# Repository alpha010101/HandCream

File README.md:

###
RP2040を使ったマイコン基板で、基本的にはRaspberry-pi pico互換。

24V系の機器を制御するのが目的で、そのために東芝のDMOS-SINKドライバTBD62064が載っている。本当ならカプラで分離するのが適当なのだろうが、こんなもんで問題なく動いてる

電源は24VをXHコネクタから入れる想定。それをTIのUA78M05で5V/0.5Aに落とし、それを更にMicrochipのMIC5504で3.3V/0.3Aに落としている。3.3VはMCU用、5VはLEDと冷却ファンの駆動用

SchematicsとPCB-LayoutはAutodesk-Eagle無償版を使用し、elecrowで製造することを想定したガーバーを作成している

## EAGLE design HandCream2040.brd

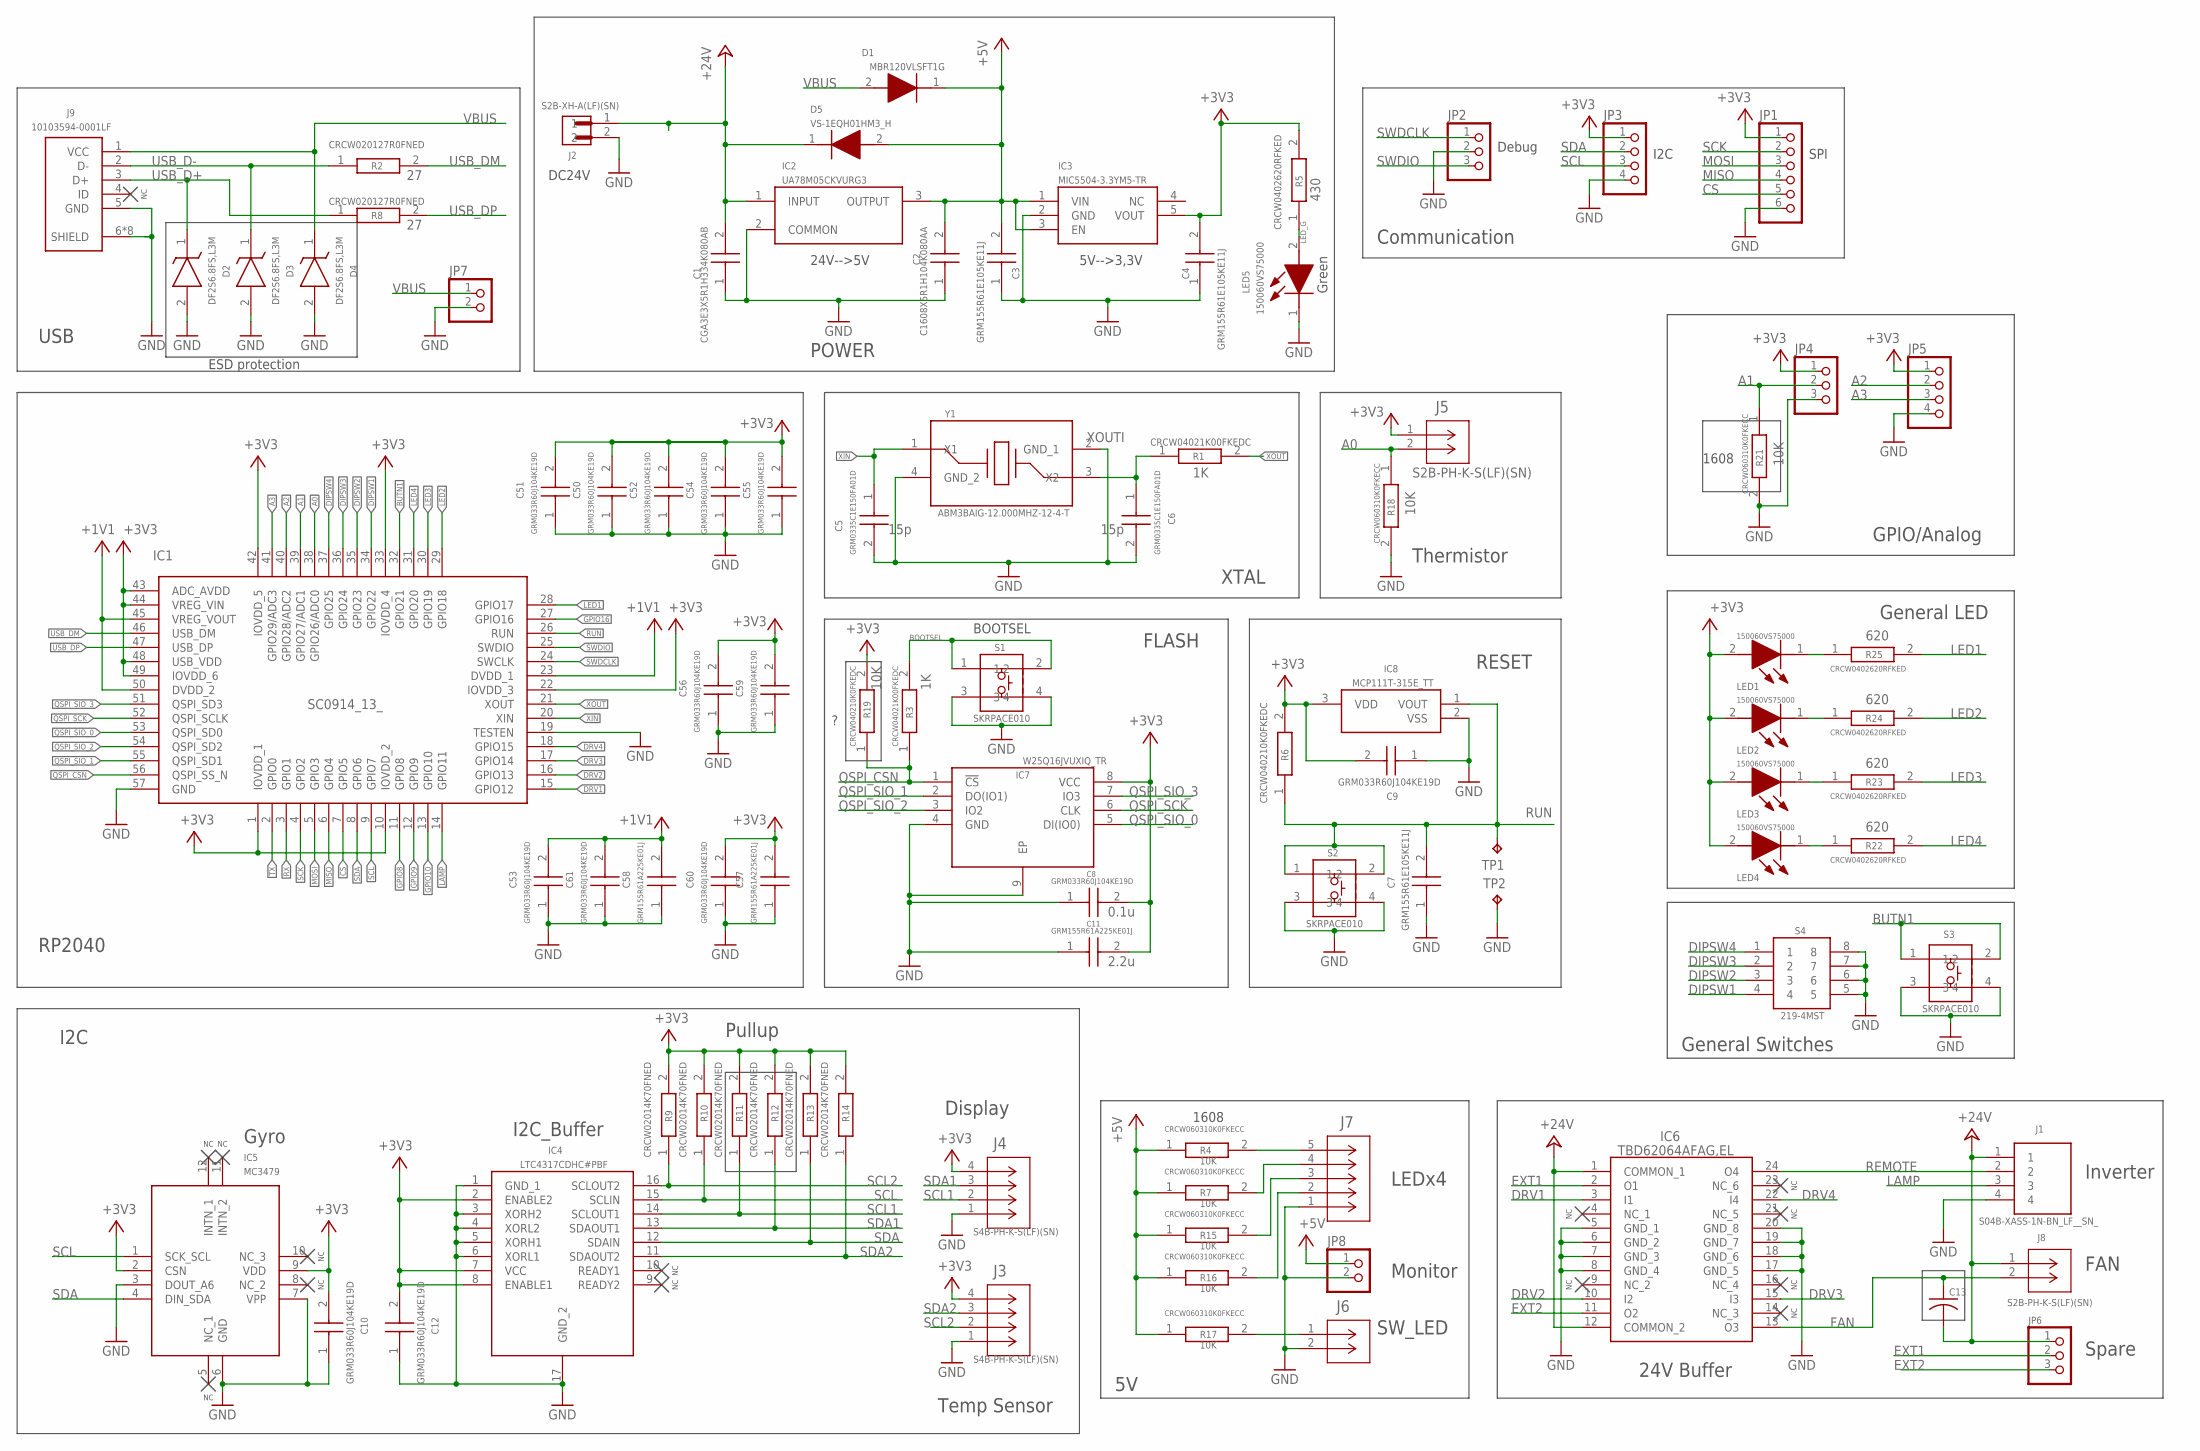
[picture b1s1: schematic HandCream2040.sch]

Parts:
C1: CGA3E3X5R1H334K080AB; CAPC1608X90N
C2: C1608X5R1H104K080AA; CAPC1608X80N
C3, C4, C7: GRM155R61E105KE11J; CAPC1005X55N
C5, C6: GRM0335C1E150FA01D; CAPC0603X33N
C8, C9, C10, C12, C50, C51, C52, C53, C54, C55, C56, C59, C60, C61: GRM033R60J104KE19D; CAPC0603X33N
C11, C57, C58: GRM155R61A225KE01J; CAPC1005X55N
C13: C-US025-024X044; C025-024X044
D1: MBR120VLSFT1G; SODFL3616X98N
D2, D3, D4: DF2S6.8FS,L3M; SODFL1006X45N
D5: VS-1EQH01HM3_H; VS1EQH01HM3H
IC1: SC0914_13_; SC091413
IC2: UA78M05CKVURG3; TPS7A6533QKVURQ1
IC3: MIC5504-3.3YM5-TR; SOT95P280X145-5N
IC4: LTC4317CDHC#PBF; SON50P300X500X80-17N
IC5: MC3479
IC6: TBD62064AFAG,EL; SOP100P800X190-24N
IC7: W25Q16JVUXIQ_TR; SON50P300X200X60-9N
IC8: MCP111T-315E_TT; SOT96P237X112-3N
J1: S04B-XASS-1N-BN_LF__SN_; S04BXASS1NBNLFSN
J2: S2B-XH-A(LF)(SN); JST_S2B-XH-A(LF)(SN)
J3, J4: S4B-PH-K-S(LF)(SN); CONN_S4B-PH-K-S_JST
J5, J6, J8: S2B-PH-K-S(LF)(SN); CONN_S2B-PH-K-S_JST
J7: S5B-PH-K-S_(LF)(SN); CONN_S5B-PH-K-S_JST
J9: 10103594-0001LF; AMPHENOL_10103594-0001LF
JP1: PINHD-1X6; 1X06
JP2, JP4, JP6: PINHD-1X3; 1X03
JP3, JP5: PINHD-1X4; 1X04
JP7, JP8: PINHD-1X2; 1X02
LED1, LED2, LED3, LED4, LED5: 150060VS75000; LEDC1608X80N
R1, R3: CRCW04021K00FKEDC; RESC1005X35N
R2, R8: CRCW020127R0FNED; RESC0603X28N
R4, R7, R15, R16, R17, R18, R21: CRCW060310K0FKECC; RESC1608X55N
R5, R22, R23, R24, R25: CRCW0402620RFKED; RESC1005X40N
R6, R19: CRCW040210K0FKEDC; RESC1005X35N
R9, R10, R11, R12, R13, R14: CRCW02014K70FNED; RESC0603X28N
S1, S2, S3: SKRPACE010; SMT(4.2X3.2)
S4: 219-4MST; 2194MST
TP1, TP2: TPB1,27; B1,27
Y1: ABM3BAIG-12.000MHZ-12-4-T; ABM3BAIG

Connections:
+1V1: C53.2, C58.2, C61.2, IC1.23 (DVDD_1), IC1.45 (VREG_VOUT), IC1.50 (DVDD_2)
+3V3: C4.2, C8.2, C9.2, C10.2, C11.2, C12.2, C50.2, C51.2, C52.2, C54.2, C55.2, C56.2, C57.2, C59.2, C60.2, IC1.1 (IOVDD_1), IC1.10 (IOVDD_2), IC1.22 (IOVDD_3), IC1.33 (IOVDD_4), IC1.42 (IOVDD_5), IC1.43 (ADC_AVDD), IC1.44 (VREG_VIN), IC1.48 (USB_VDD), IC1.49 (IOVDD_6), IC3.5 (VOUT), IC4.2 (ENABLE2), IC4.7 (VCC), IC4.8 (ENABLE1), IC5.2 (CSN), IC5.9 (VDD), IC7.8 (VCC), IC8.3 (VDD), J3.4, J4.4, J5.1, JP1.1, JP3.1, JP4.1, JP5.1, LED1.2 (A), LED2.2 (A), LED3.2 (A), LED4.2 (A), R5.2, R6.2, R9.2, R10.2, R11.2, R12.2, R13.2, R14.2, R19.2
+5V: C2.2, C3.2, D1.1 (K), D5.2 (A), IC2.3 (OUTPUT), IC3.1 (VIN), IC3.3 (EN), JP8.1, R4.1, R7.1, R15.1, R16.1, R17.1
+24V: C1.2, C13.2, D5.1 (K), IC2.1 (INPUT), IC6.1 (COMMON_1), IC6.12 (COMMON_2), J1.1, J2.1, J8.1, JP6.1
A0: IC1.38 (GPIO26/ADC0), J5.2, R18.1
A1: IC1.39 (GPIO27/ADC1), JP4.2, R21.1
A2: IC1.40 (GPIO28/ADC2), JP5.2
A3: IC1.41 (GPIO29/ADC3), JP5.3
BOOTSEL: R3.2, S1.1, S1.2
BUTN1: IC1.32 (GPIO21), S3.1, S3.2
CS: IC1.7 (GPIO5), JP1.5
DIPSW1: IC1.34 (GPIO22), S4.4
DIPSW2: IC1.35 (GPIO23), S4.3
DIPSW3: IC1.36 (GPIO24), S4.2
DIPSW4: IC1.37 (GPIO25), S4.1
DRV1: IC1.15 (GPIO12), IC6.3 (I1)
DRV2: IC1.16 (GPIO13), IC6.10 (I2)
DRV3: IC1.17 (GPIO14), IC6.15 (I3)
DRV4: IC1.18 (GPIO15), IC6.22 (I4)
EXT1: IC6.2 (O1), JP6.2
EXT2: IC6.11 (O2), JP6.3
FAN: C13.1, IC6.13 (O3), J8.2
GND: C1.1, C2.1, C3.1, C4.1, C5.2, C6.2, C7.1, C8.1, C9.1, C10.1, C11.1, C12.1, C50.1, C51.1, C52.1, C53.1, C54.1, C55.1, C56.1, C57.1, C58.1, C59.1, C60.1, C61.1, D2.2 (A), D3.2 (A), D4.2 (A), IC1.19 (TESTEN), IC1.57 (GND), IC2.2 (COMMON), IC3.2 (GND), IC4.1 (GND_1), IC4.3 (XORH2), IC4.4 (XORL2), IC4.5 (XORH1), IC4.6 (XORL1), IC4.17 (GND_2), IC5.3 (DOUT_A6), IC5.6 (GND), IC5.7 (VPP), IC6.5 (GND_1), IC6.6 (GND_2), IC6.7 (GND_3), IC6.8 (GND_4), IC6.17 (GND_5), IC6.18 (GND_6), IC6.19 (GND_7), IC6.20 (GND_8), IC7.4 (GND), IC7.9 (EP), IC8.2 (VSS), J1.4, J2.2, J3.1, J4.1, J6.2, J7.1, J9.5 (GND), J9.6 (SHIELD), J9.7 (SHIELD), J9.8 (SHIELD), J9.9 (SHIELD), J9.10 (SHIELD), J9.11 (SHIELD), J9.S1 (SHIELD), J9.S2 (SHIELD), JP1.6, JP2.2, JP3.4, JP4.3, JP5.4, JP7.2, JP8.2, LED5.1 (K), R18.2, R21.2, S1.3, S1.4, S2.3, S2.4, S3.3, S3.4, S4.5, S4.6, S4.7, S4.8, TP2.TP, Y1.2 (GND_1), Y1.4 (GND_2)
GPIO8: IC1.11 (GPIO8)
GPIO9: IC1.12 (GPIO9)
GPIO10: IC1.13 (GPIO10)
GPIO16: IC1.27 (GPIO16)
LAMP: IC1.14 (GPIO11), J1.3
LED1: IC1.28 (GPIO17), R25.2
LED2: IC1.29 (GPIO18), R24.2
LED3: IC1.30 (GPIO19), R23.2
LED4: IC1.31 (GPIO20), R22.2
LED_G: LED5.2 (A), R5.1
MISO: IC1.6 (GPIO4), JP1.4
MOSI: IC1.5 (GPIO3), JP1.3
unnamed: J7.5, R4.2
unnamed: J7.4, R7.2
unnamed: J7.3, R15.2
unnamed: J7.2, R16.2
unnamed: J6.1, R17.2
unnamed: LED1.1 (K), R25.1
unnamed: LED2.1 (K), R24.1
unnamed: LED3.1 (K), R23.1
unnamed: LED4.1 (K), R22.1
QSPI_CSN: IC1.56 (QSPI_SS_N), IC7.1 (!CS), R3.1, R19.1
QSPI_SCK: IC1.52 (QSPI_SCLK), IC7.6 (CLK)
QSPI_SIO_0: IC1.53 (QSPI_SD0), IC7.5 (DI(IO0))
QSPI_SIO_1: IC1.55 (QSPI_SD1), IC7.2 (DO(IO1))
QSPI_SIO_2: IC1.54 (QSPI_SD2), IC7.3 (IO2)
QSPI_SIO_3: IC1.51 (QSPI_SD3), IC7.7 (IO3)
REMOTE: IC6.24 (O4), J1.2
RUN: C7.2, IC1.26 (RUN), IC8.1 (VOUT), R6.1, S2.1, S2.2, TP1.TP
RX: IC1.3 (GPIO1)
SCK: IC1.4 (GPIO2), JP1.2
SCL: IC1.9 (GPIO7), IC4.15 (SCLIN), IC5.1 (SCK_SCL), JP3.3, R10.1
SCL1: IC4.14 (SCLOUT1), J4.2, R11.1
SCL2: IC4.16 (SCLOUT2), J3.2, R9.1
SDA: IC1.8 (GPIO6), IC4.12 (SDAIN), IC5.4 (DIN_SDA), JP3.2, R13.1
SDA1: IC4.13 (SDAOUT1), J4.3, R12.1
SDA2: IC4.11 (SDAOUT2), J3.3, R14.1
SWDCLK: IC1.24 (SWCLK), JP2.1
SWDIO: IC1.25 (SWDIO), JP2.3
TX: IC1.2 (GPIO0)
USB_D+: D2.1 (K), J9.3 (D+), R8.1
USB_D-: D3.1 (K), J9.2 (D-), R2.1
USB_DM: IC1.46 (USB_DM), R2.2
USB_DP: IC1.47 (USB_DP), R8.2
VBUS: D1.2 (A), D4.1 (K), J9.1 (VCC), JP7.1
XIN: C5.1, IC1.20 (XIN), Y1.1 (X1)
XOUT: IC1.21 (XOUT), R1.2
XOUTI: C6.1, R1.1, Y1.3 (X2)

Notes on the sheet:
USB
POWER
RP2040
FLASH
XTAL
RESET
BOOTSEL
I2C
Gyro
Display
Temp Sensor
LEDx4
SW_LED
24V Buffer
Monitor
Inverter
FAN
Spare
Thermistor
General Switches
Green
24V-->5V
5V-->3,3V
DC24V
Debug
I2C_Buffer
Pullup
General LED
SPI
Communication
GPIO/Analog
ESD protection
1608

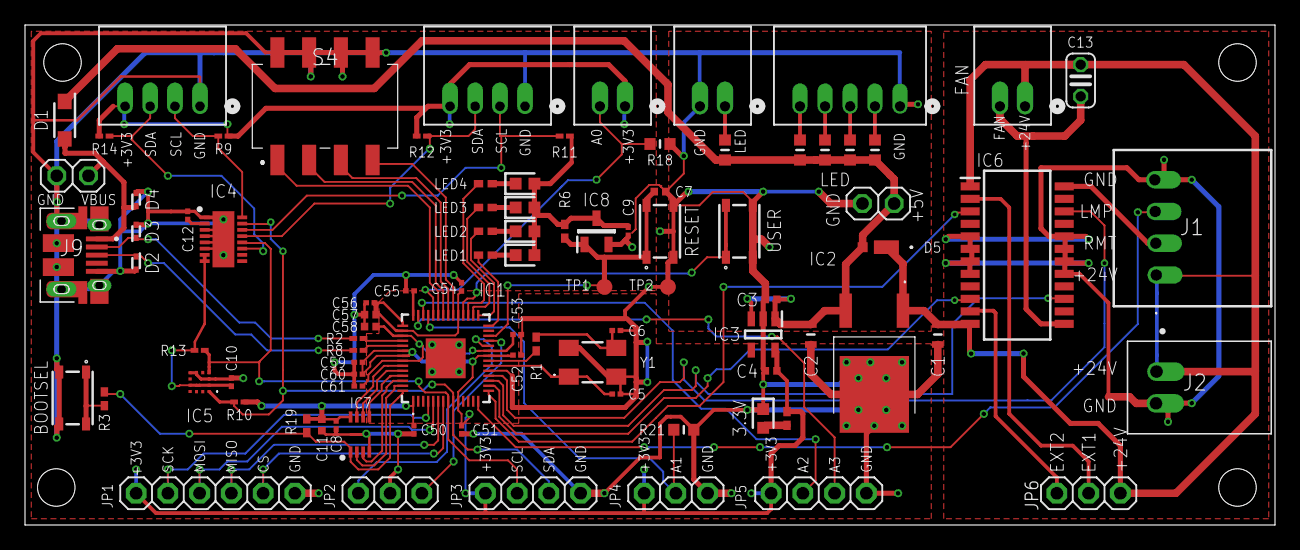
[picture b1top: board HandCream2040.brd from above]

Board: 2 copper layers, 100.0 x 40.0 mm, 91 parts (0 on the bottom side), 65 nets.

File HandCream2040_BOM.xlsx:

| Part# | Device | Qty | Manufacturer | Package | Value | Description | Source | MOUSER_PART_NUMBER | MOUSER_PRICE-STOCK
 | C1 | CGA3E3X5R1H334K080AB | 1 | TDK | CAPC1608X90N | 0.33uF | Multilayer Ceramic Capacitor, 50V, 10%, X5R, 1608 (0603), Or equivalent | mouser or Elecrow | 810-CGA3E3X5R1H334KB | https://www.mouser.co.uk/ProductDetail/TDK/CGA3E3X5R1H334K08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
 | C2 | C1608X5R1H104K080AA | 1 | TDK | CAPC1608X80N | 0.1uF | Multilayer Ceramic Capacitor, 50V, 10%, X5R, 1608 (0603), Or equivalent | mouser or Elecrow | 810-C1608X5R1H104K | https://www.mouser.co.uk/ProductDetail/TDK/C1608X5R1H104K080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
 | C3,C4,C7 | GRM155R61E105KE11J | 3 | Murata Electronics | CAPC1005X55N | 1uF | Multilayer Ceramic Capacitor, 25V, 10%, X5R, 1005 (0402), Or equivalent | mouser or Elecrow | 81-GRM155R61E105KE1J | https://www.mouser.co.uk/ProductDetail/Murata-Electronics/GR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
 | C5,C6 | GRM0335C1E150FA01D | 2 | Murata Electronics | CAPC0603X33N | 15pF | Multilayer Ceramic Capacitor, 25V, 1%, C0G, 0603 (0201), Or equivalent | mouser or Elecrow | 81-GRM0335C1E150FA1D | https://www.mouser.co.uk/ProductDetail/Murata-Electronics/GR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
 | C8,C9,C10,C12,C50,C51,C52, C53,C54,C55,C56,C59,C60,C61 | GRM033R60J104KE19D | 14 | Murata Electronics | CAPC0603X33N | 0.1uF | Multilayer Ceramic Capacitor, 6.3V, 10%, X5R, 0603 (0201), Or equivalent | mouser or Elecrow | 81-GRM033R60J104KE19 | https://www.mouser.co.uk/ProductDetail/Murata-Electronics/GR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
 | C11,C57,C58 | GRM155R61A225KE01J | 3 | Murata Electronics | CAPC1005X55N | 2.2uF | Multilayer Ceramic Capacitor, 10V, 10%, X5R, 1005 (0402), Or equivalent | mouser or Elecrow | 81-GRM155R61A225K01J | https://www.mouser.co.uk/ProductDetail/Murata-Electronics/GR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
 | C13 |  | 0 |  |  |  | No need to assemble
 | D1 | MBR120VLSFT1G | 1 | onsemi | SODFL3616X98N |  | Diode Schottky 20V, 1A, SOD-123FL | mouser or Elecrow | 863-MBR120VLSFT1G | https://www.mouser.co.uk/ProductDetail/onsemi/MBR120VLSFT1G?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
 | D2,D3,D4 | DF2S6.8FS,L3M | 0 | Toshiba | SODFL1006X45N |  | No need to assemble
 | D5 | VS-1EQH01HM3_H | 1 | Vishay | VS1EQH01HM3H |  | Rectifiers 100V 1A Fred Pt MicroSMP (DO-219AD) | mouser or Elecrow | 78-VS-1EQH01HM3/H | https://www.mouser.co.uk/ProductDetail/Vishay-Semiconductors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
 | IC1 | SC0914(13) / RP2040 | 1 | RASPBERRY-PI | SC091413 |  | ARM Cortex-M0+ - Microcontroller IC 32-Bit Dual-Core 133MHz External Program Me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 | mouser or Elecrow | 358-SC091413 | https://www.mouser.co.uk/ProductDetail/Raspberry-Pi/SC091413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
 | IC2 | UA78M05CKVURG3 | 1 | Texas Instruments | TPS7A6533QKVURQ1 |  | Linear Voltage Regulators, 500mA, 5V-output, max25V, | mouser or Elecrow | 595-UA78M05CKVURG3 | https://www.mouser.co.uk/ProductDetail/Texas-Instruments/UA7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
 | IC3 | MIC5504-3.3YM5-TR | 1 | Microchip | SOT95P280X145-5N |  | LDO Voltage Regulators, 300mA, 3.3V-output, max5.5V, SOT-23-5 | mouser or Elecrow | 998-MIC5504-3.3YM5TR | https://www.mouser.co.uk/ProductDetail/Microchip-Technology/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
 | IC4 | LTC4317CDHC#PBF | 1 | Analog Devices | SON50P300X500X80-17N |  | Specialized Interface, I2C, SMBus, I2C Bus & SMBus Systems Applications, Server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 | mouser or Elecrow | 584-LTC4317CDHC#PBF | https://www.mouser.com/Search/Refine.aspx?Keyword=584-LTC431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
 | IC5 | MC3479 | 1 | MEMSIC | MC3479 |  | Accelerometers Small Digital 3-axis Accelerometer Sensor | mouser or Elecrow | 498-MC3479 | https://www.mouser.co.uk/ProductDetail/MEMSIC/MC3479?qs=OlC7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
 | IC6 | TBD62064AFAG,EL | 1 | Toshiba | SOP100P800X190-24N |  | Gate Drivers DMOS Transistor Array 50V 1500mA | mouser or Elecrow | 757-TBD62064AFAGEHZ | https://www.mouser.co.uk/ProductDetail/Toshiba/TBD62064AFAGE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
 | IC7 | W25Q16JVUXIQ_TR | 1 | Winbond | SON50P300X200X60-9N |  | NOR Flash spiFlash, 3V, 16M-bit, 4Kb Uniform Sector, DTR | mouser or Elecrow | 454-W25Q16JVUXIQTR | https://www.mouser.co.uk/ProductDetail/Winbond/W25Q16JVUXIQ-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
 | IC8 | MCP111T-315E_TT | 1 | Microchip | SOT96P237X112-3N |  | Voltage Supervisor 3.003 3.157 V, 3-Pin SOT-23B | mouser or Elecrow | 579-MCP111T-315E/TT | https://www.mouser.co.uk/ProductDetail/Microchip-Technology/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
 | J1 | S04B-XASS-1N-BN_LF__SN_ | 0 | JST | S04BXASS1NBNLFSN |  | No need to assemble
 | J2 | S2B-XH-A(LF)(SN) | 0 | JST | JST_S2B-XH-A(LF)(SN) |  | No need to assemble
 | J3,J4 | S4B-PH-K-S(LF)(SN) | 0 | JST | CONN_S4B-PH-K-S_JST |  | No need to assemble
 | J5,J6,J8 | S2B-PH-K-S(LF)(SN) | 0 | JST | CONN_S2B-PH-K-S_JST |  | No need to assemble
 | J7 | S5B-PH-K-S_(LF)(SN) | 0 | JST | CONN_S5B-PH-K-S_JST |  | No need to assemble
 | J9 | 10103594-0001LF | 1 | Amphenol ICC | AMPHENOL_10103594-0001LF |  | USB - micro B USB 2.0 Receptacle Connector 5 Position Surface Mount, Right Angl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 | mouser or Elecrow
 | LED1,LED2,LED3,LED4,LED5 | 150060VS75000 | 5 | Wurth Elektronik | LEDC1608X80N |  | Green LED, 2V/20mA, 1608 (0603) | mouser or Elecrow | 710-150060VS75000 | https://www.mouser.co.uk/ProductDetail/Wurth-Elektronik/1500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
 | R1,R3 | CRCW04021K00FKEDC | 2 | Vishay | RESC1005X35N | 1KΩ | Thick Film Resistor, 1005(0402), 1K, 1%, 0.063W(1/16W), Or equivalent | mouser or Elecrow | 71-CRCW04021K00FKEDC | https://www.mouser.co.uk/ProductDetail/Vishay-Dale/CRCW04021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
 | R2,R8 | CRCW020127R0FNED | 2 | Vishay | RESC0603X28N | 27Ω | Thick Film Resistor, 0603(0201), 27, 1%, 0.05W(1/20W), Or equivalent | mouser or Elecrow | 71-CRCW020127R0FNED | https://www.mouser.co.uk/ProductDetail/Vishay-Dale/CRCW02012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
 | R4,R7,R15,R16, R17,R18 | CRCW060310K0FKECC | 6 | Vishay | RESC1608X55N | 10KΩ | Thick Film Resistor, 1608(0603), 10K, 1%, 0.1W(1/10W), Or equivalent | mouser or Elecrow | 71-CRCW060310K0FKECC | https://www.mouser.co.uk/ProductDetail/Vishay-Dale/CRCW06031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
 | R21 | CRCW060310K0FKECC | 0 | Vishay | RESC1608X55N | 10KΩ | No need to assemble (pulldown)
 | R6,R19 | CRCW040210K0FKEDC | 2 | Vishay | RESC1005X35N | 10KΩ | Thick Film Resistor, 1005(0402), 10K, 1%, 0.063W(1/16W), Or equivalent | mouser or Elecrow | 71-CRCW040210K0FKEDC | https://www.mouser.co.uk/ProductDetail/Vishay-Dale/CRCW04021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
 | R9,R10,R13,R14 | CRCW02014K70FNED | 4 | Vishay | RESC0603X28N | 4.7KΩ | Thick Film Resistor, 0603(0201), 4.7K, 1%, 0.05W(1/20W), Or equivalent | mouser or Elecrow | 71-CRCW02014K70FNED | https://www.mouser.co.uk/ProductDetail/Vishay-Dale/CRCW02014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
 | R11,R12 | CRCW02014K70FNED | 0 | Vishay | RESC0603X28N | 4.7KΩ | No need to assemble (I2C pullup)
 | R5,R22,R23,R24,R25 | CRCW0402620RFKED | 5 | Vishay | RESC1005X40N | 620Ω | Thick Film Resistor 1005(0402), 620, 1%, 0.063W(1/16W), Or equivalent | mouser or Elecrow | 71-CRCW0402-620-E3 | https://www.mouser.com/Search/Refine.aspx?Keyword=71-CRCW040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
 | S1,S2,S3 | SKRPACE010 | 3 | ALPS Electric | SMT(4.2X3.2) |  | Tactile Switches 4.2x3.2x2.5mm 260gf | mouser or Elecrow | 688-SKRPACE010 | https://www.mouser.co.uk/ProductDetail/Alps-Alpine/SKRPACE01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
 | S4 | 219-4MST | 1 | CTS | 2194MST |  | DIP Switches / SIP Switches | mouser or Elecrow | 774-2194MST | https://www.mouser.co.uk/ProductDetail/CTS-Electronic-Compon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
 | Y1 | ABM3BAIG-12.000MHZ-12-4-T | 1 | ABRACON | ABM3BAIG |  | 12 MHz +/-30ppm Crystal 12pF 70 Ohms 4-SMD, No Lead | mouser or Elecrow | 815-ABM3BAIG1212-4T | https://www.mouser.co.uk/ProductDetail/ABRACON/ABM3BAIG-1200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

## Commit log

2024-12-31 initial release

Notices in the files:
parts and their libraries:
COPYRIGHT: Copyright (C) 2023 Ultra Librarian. All rights reserved.
